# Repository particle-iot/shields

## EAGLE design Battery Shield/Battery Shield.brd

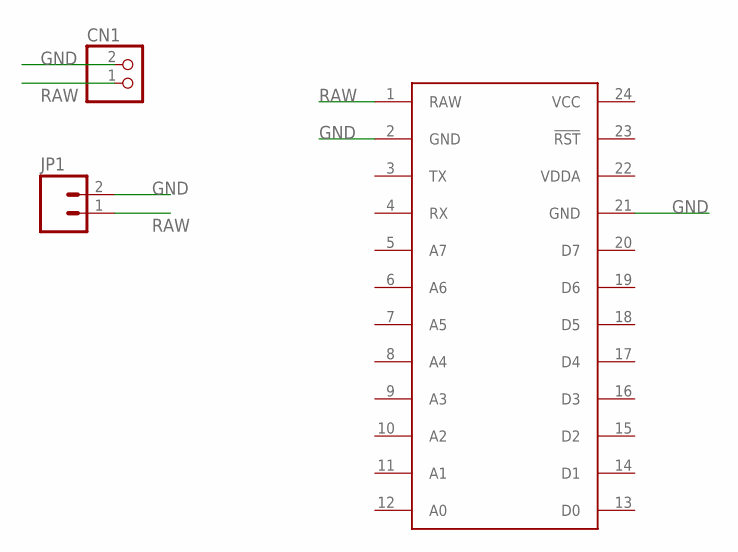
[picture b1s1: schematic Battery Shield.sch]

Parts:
CN1: JST_2PIN-THM; JST-PH-2-THM
JP1: M02PTH4; 1X02_XTRA_BIG
U$1: SPARK_CORECORE; SPARK_CORE

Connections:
GND: CN1.2 (1), JP1.2, U$1.2 (GND), U$1.21 (GND)
RAW: CN1.1 (2), JP1.1, U$1.1 (RAW)
VCC: U$1.24 (VCC)
VDDA: U$1.22 (VDDA)

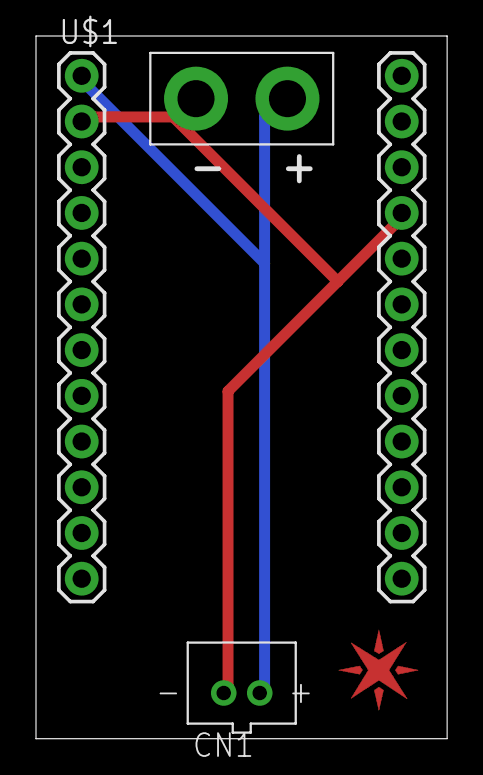
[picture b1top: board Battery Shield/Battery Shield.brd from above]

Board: 2 copper layers, 22.8 x 39.0 mm, 4 parts (0 on the bottom side), 2 nets.

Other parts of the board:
U$2: SPARK_LOGO_PLUS_PLANE

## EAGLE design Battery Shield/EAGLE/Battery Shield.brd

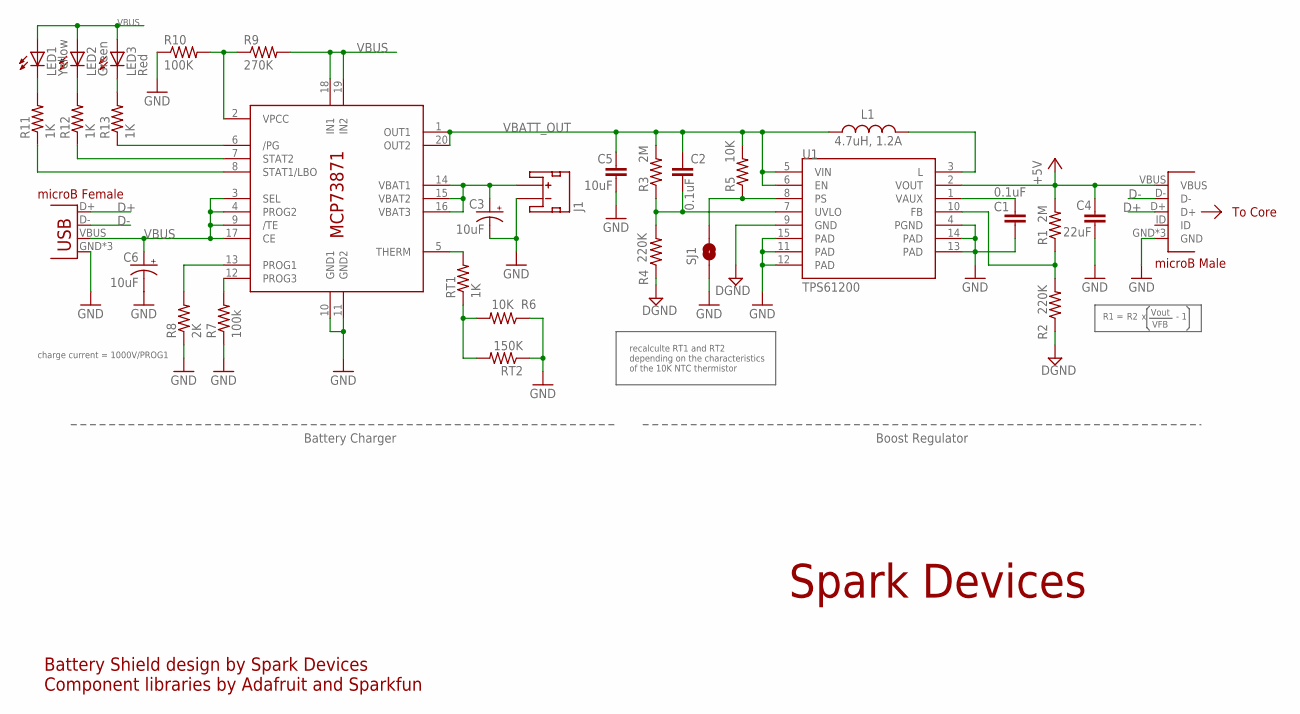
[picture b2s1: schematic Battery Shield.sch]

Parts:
C1, C2: 0.1uF; 0402-CAP
C3, C6: 10uF; EIA3216
C4: 22uF; 0805
C5: 10uF; 1206
IC1: MCP73871; QFN20
J1: JST_2MM_MALE; JST-2-SMD
JP1: USBUSB-MICROB-SLOT-HOLE; USB-MICROB-SLOT-HOLE
L1: 4.7uH, 1.2A; CDRH2D09
LED1: Yellow; LED-0603
LED2: Green; LED-0603
LED3: Red; LED-0603
R1, R3: 2M; 0402-RES
R2, R4: 220K; 0402-RES
R5, R6: 10K; 0402-RES
R7: 100k; 0402-RES
R8: 2K; 0402-RES
R9: 270K; 0402-RES
R10: 100K; 0402-RES
R11, R12, R13: 1K; 0402-RES
RT1: 1K; 0402-RES
RT2: 150K; 0402-RES
SJ1: SOLDERJUMPERNO; SJ_2S-NO
U1: TPS61200; QFN-10_PAD
U$1: USB_MALE; USB-MICROB-MALE-SANDWICH

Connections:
+5V: C4.1, R1.2, U1.2 (VOUT), U$1.VBUS; also elsewhere on the board
D+: JP1.D+, U$1.D+; also elsewhere on the board
D-: JP1.D-, U$1.D-; also elsewhere on the board
DGND: R2.1, R4.1, U1.9 (GND)
GND: C1.2, C3.C (-), C4.2, C5.2, C6.C (-), IC1.10 (GND1), IC1.11 (GND2), J1.1 (-), JP1.GND, JP1.MT1 (GND), JP1.MT2 (GND), R6.1, R7.1, R8.1, R10.1, RT2.1, SJ1.1, U1.4 (PGND), U1.11 (PAD), U1.12 (PAD), U1.13 (PAD), U1.14 (PAD), U1.15 (PAD), U$1.GND; also elsewhere on the board
unnamed: L1.P$2 (2), U1.3 (L)
unnamed: C1.1, U1.1 (VAUX)
unnamed: C2.2, R3.1, R4.2, U1.7 (UVLO)
unnamed: R1.1, R2.2, U1.10 (FB)
unnamed: C3.A (+), IC1.14 (VBAT1), IC1.15 (VBAT2), IC1.16 (VBAT3), J1.2 (+)
unnamed: IC1.8 (STAT1/LBO), R11.1
unnamed: R6.2, RT1.1, RT2.2
unnamed: LED1.C, R11.2
unnamed: IC1.5 (THERM), RT1.2
unnamed: LED2.C, R12.2
unnamed: IC1.12 (PROG3), R7.2
unnamed: IC1.2 (VPCC), R9.1, R10.2
unnamed: IC1.13 (PROG1), R8.2
unnamed: IC1.7 (STAT2), R12.1
unnamed: IC1.6 (/PG), R13.1
unnamed: LED3.C, R13.2
unnamed: R5.1, SJ1.2, U1.8 (PS)
VBATT_OUT: C2.1, C5.1, IC1.1 (OUT1), IC1.20 (OUT2), L1.P$1 (1), R3.2, R5.2, U1.5 (VIN), U1.6 (EN)
VBUS: C6.A (+), IC1.3 (SEL), IC1.4 (PROG2), IC1.9 (/TE), IC1.17 (CE), IC1.18 (IN1), IC1.19 (IN2), JP1.VBUS, LED1.A, LED2.A, LED3.A, R9.2

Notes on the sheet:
microB Male
microB Female
To Core
Battery Charger
Boost Regulator
recalculte RT1 and RT2 depending on the characteristics of the 10K NTC thermistor
charge current = 1000V/PROG1
R1 =
Vout
VFB
- 1
Spark Devices
Battery Shield design by Spark Devices Component libraries by Adafruit and Sparkfun

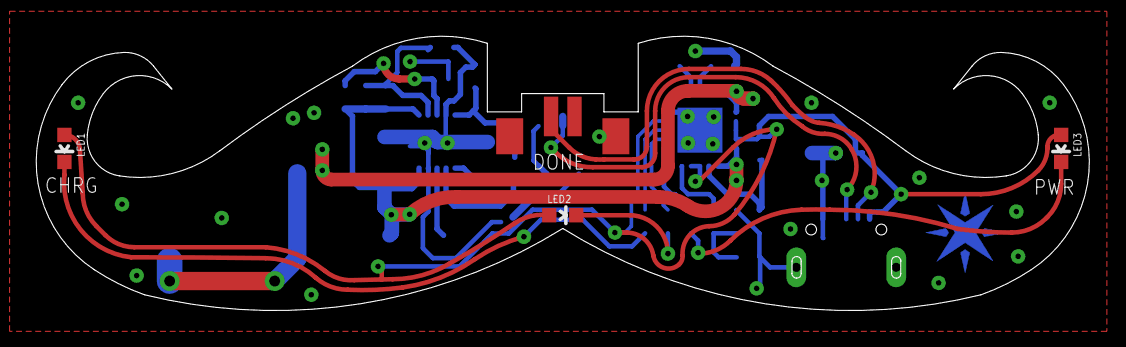
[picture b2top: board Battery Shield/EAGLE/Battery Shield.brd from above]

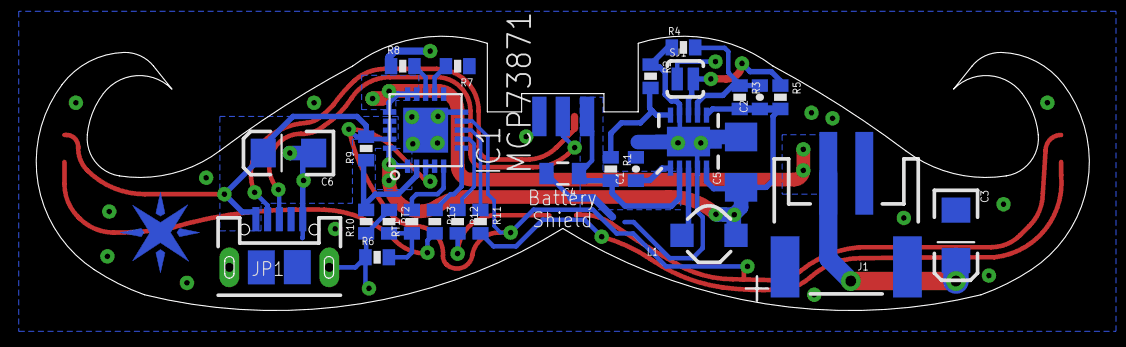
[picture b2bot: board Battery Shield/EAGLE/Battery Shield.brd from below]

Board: 2 copper layers, 58.5 x 15.2 mm, 32 parts (28 on the bottom side), 24 nets.

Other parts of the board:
JP2: USBFCI; USB-MICROB-MALE-SANDWICH
U$2: SPARK_LOGO_PLUS_PLANE

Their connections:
+5V: JP2.VBUS; also elsewhere on the board
D+: JP2.D+; also elsewhere on the board
D-: JP2.D-; also elsewhere on the board
GND: JP2.GND, JP2.GNDPAD1, JP2.GNDPAD2; also elsewhere on the board

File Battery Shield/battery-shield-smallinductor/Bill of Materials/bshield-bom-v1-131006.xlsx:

| PROJECT NAME |  | SPARK BATTERY SHIELD
 | LAST UPDATED |  | 41554
 | BSHIELD
 | Qty | AQS P/N | Device | Minimum Specification | Component Value (if different) | Package/Case | Designator | AVL | AVL P/N | Additional Comments
 | 1 | 307-20-301621 | Fab PCB | Double Sided, 1.0mm, 1OZ, Electroless Nickel Immersion Gold, Black Solder Mask,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 |  |  |  |  |  | CONSIGNED BY SPARK
 | 1 | HL-121-12-301353 | Ceramic Capacitor | 10uF, 10V, 10% |  | 1206 | C5 | Taiyo | LMK316BJ106KLHT
 | 2 | HL-121-02-301600 | Ceramic Capacitor | 0.1uF, 10V, 10% |  | 0402 | C1, C2 | RongFu | 0402B104K01A
 | 1 | HL-121-10-301613 | Ceramic Capacitor | 22uF, 10V, 10% |  | 0805 | C4 | Taiyo Yuden | LMK212BJ226MG-T
 | 1 | HL-221-90-301464 | DC to DC Booster | 1.2A |  | QFN10 Exposed Pad | U1 | Texas Instruments | TPS61200DRCT
 | 1 | 161-50-301205 | Inductor | 4.7uH, 25%, 1.0A |  | 3030 (3x3mm) | L1 | Sumida America | CDRH2D18/HPNP-4R7NC | CONSIGNED BY SPARK
 | 1 | HL-511-30-301381 | JST Right-Angle Connector | 2mm, 2-pin, Male, SMT |  | 2-Pin SMT, Right-Angle | J1 | Kaweei | CW2001-02T1-H01-B
 | 1 | HL-414-10-301291 | LED | Yellow |  | 0603 | LED1 | AQS supplier | WLUY0603A-25
 | 1 | HL-414-10-301292 | LED | Green |  | 0603 | LED2 | AQS supplier | WLG0603A-02-I
 | 1 | HL-414-10-301282 | LED | Blue |  | 0603 | LED3 | AQS supplier | WLUB0603A-341
 | 1 | HL-411-60-301004 | Li-Ion Rechargeable Battery | 3.7V, 400mAh, JST-PH-2P connector |  | JST-PH connector, 2-pin | BT1 | Pkcell | LP062530
 | 1 | 223-40-301231 | LiPo Charger | 4.4V-6.0V Input |  | QFN20 Exposed Pad (4x4) | IC1 | Microchip Technology | MCP73871T-2CCI/ML | CONSIGNED BY SPARK
 | 2 | HL-101-10-302444 | Resistor | 2M, 1%, 1/10W |  | 0402 | R1, R3 | Velox Vendor | SMD0402205F
 | 2 | HL-101-10-302445 | Resistor | 100K, 1%, 1/10W |  | 0402 | R7, R10 | Velox Vendor | SMD0402104F
 | 4 | HL-101-10-302446 | Resistor | 1K, 1%, 1/10W |  | 0402 | R11, R12, R13, RT1 | Velox Vendor | SMD0402102F
 | 2 | HL-101-10-302447 | Resistor | 220K, 1%, 1/10W |  | 0402 | R2, R4 | Velox Vendor | SMD0402223F
 | 1 | HL-101-10-302448 | Resistor | 2K, 1%, 1/10W |  | 0402 | R8 | Velox Vendor | SMD0402202F
 | 1 | HL-101-10-302449 | Resistor | 270K, 1%, 1/10W |  | 0402 | R9 | Velox Vendor | SMD0402273F
 | 1 | HL-101-10-302443 | Resistor | 150K, 1%, 1/10W |  | 0402 | RT2 | RongFu | 0402WAF0150KTCE
 | 1 | HL-101-10-302450 | Resistor | 10K, 1%, 1/10W |  | 0402 | R5, R6 | Panasonic Electronic Components | ERJ-2RKF1002X
 | 2 | HL-121-12-301350 | Tantalum Capacitor | 10uF, 16V, 10% |  | 1206 (3216) | C3, C6 | AVX | TAJA106K010RNJ.
 | 1 | HL-515-40-301729 | USB-Micro B Connector - Female | USB-Micro B, SMT with TH Board Guides |  | USB-MICROB | JP1 | Kaweei | CMCUSB-5BFM2G-01-D
 | 1 | 511-30-301385 | USB-Micro B Connector - Male | USB-Micro B, SMT with Sandwich Guides |  | USB-MICROB | JP2 | FCI | 10104109-0001LF | CONSIGNED BY SPARK
 | PACKAGING
 | Qty |  | Device | Minimum Specification | Component Value (if different) | Package/Case | Designator | AVL | AVL P/N | Additional Comments
 | 1 | HL-901-00-301327 | Small Static Bag |  |  | 130 x 100mm
 | 1 | HL-901-00-301332 | Small Static Bubble Bag |  |  | 110 x 140mm, red
 | 1 | 831-10-301388 | "STICK-BS" sticker | Shield Description and UPC Barcode |  | 8 x 10 cm |  |  |  | CONSIGNED BY SPARK

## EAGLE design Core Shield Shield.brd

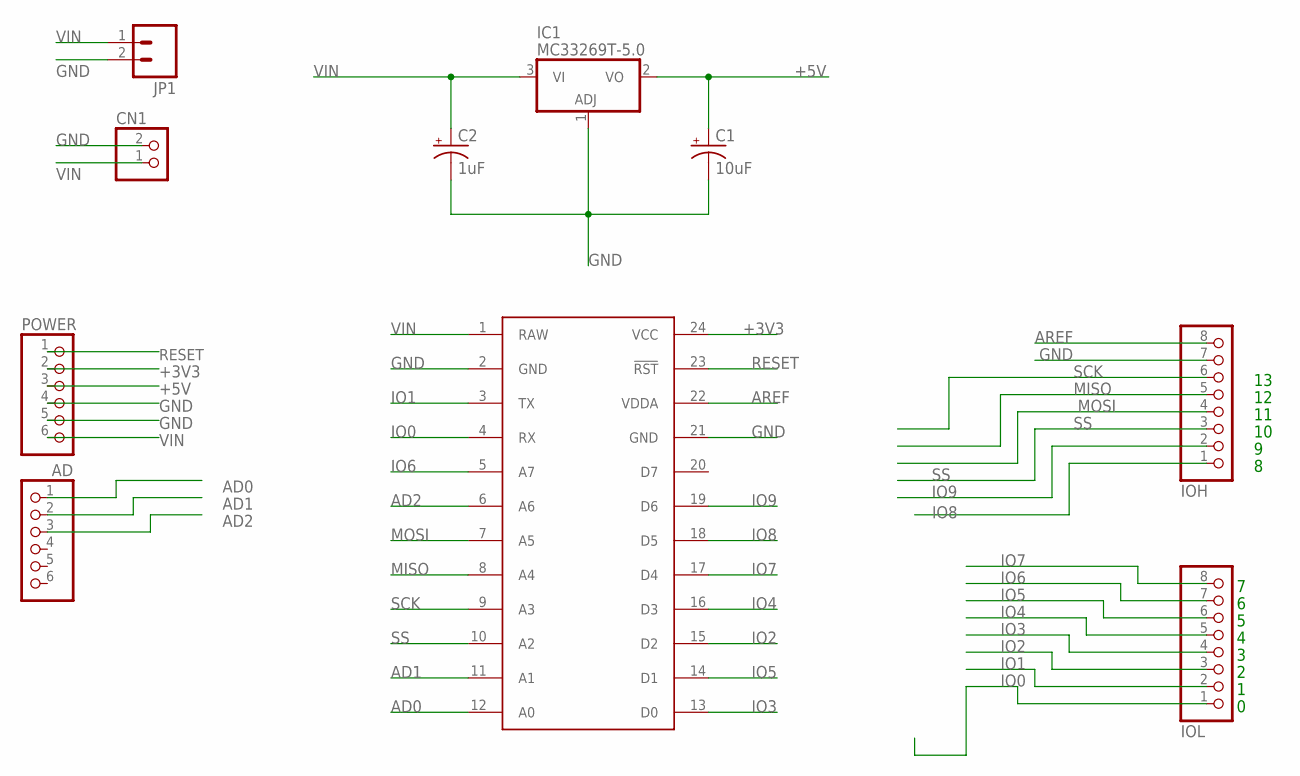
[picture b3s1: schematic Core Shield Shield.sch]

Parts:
AD: PINHD-1X6; 1X06
C1: 10uF; CPOL-RADIAL-10UF-25V
C2: 1uF; CPOL-RADIAL-10UF-25V
CN1: JST_2PIN-THM; JST-PH-2-THM
IC1: MC33269T-5.0; TO220V
IOH: PINHD-1X8; 1X08
IOL: PINHD-1X8; 1X08
JP1: M02LOCK; 1X02_LOCK
POWER: PINHD-1X6; 1X06
U$1: SPARK_CORECORE; SPARK_CORE

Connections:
+3V3: POWER.2, U$1.24 (VCC)
+5V: C1.1 (+), IC1.2 (VO), POWER.3
AD0: AD.1, U$1.12 (A0)
AD1: AD.2, U$1.11 (A1)
AD2: AD.3, U$1.6 (A6)
AREF: IOH.8, U$1.22 (VDDA)
GND: C1.2 (-), C2.2 (-), CN1.2 (1), IC1.1 (ADJ), IOH.7, JP1.2, POWER.4, POWER.5, U$1.2 (GND), U$1.21 (GND)
IO0: IOL.1, U$1.4 (RX)
IO1: IOL.2, U$1.3 (TX)
IO2: IOL.3, U$1.15 (D2)
IO3: IOL.4, U$1.13 (D0)
IO4: IOL.5, U$1.16 (D3)
IO5: IOL.6, U$1.14 (D1)
IO6: IOL.7, U$1.5 (A7)
IO7: IOL.8, U$1.17 (D4)
IO8: IOH.1, U$1.18 (D5)
IO9: IOH.2, U$1.19 (D6)
MISO: IOH.5, U$1.8 (A4)
MOSI: IOH.4, U$1.7 (A5)
RESET: POWER.1, U$1.23 (!RST)
SCK: IOH.6, U$1.9 (A3)
SS: IOH.3, U$1.10 (A2)
VIN: C2.1 (+), CN1.1 (2), IC1.3 (VI), JP1.1, POWER.6, U$1.1 (RAW)

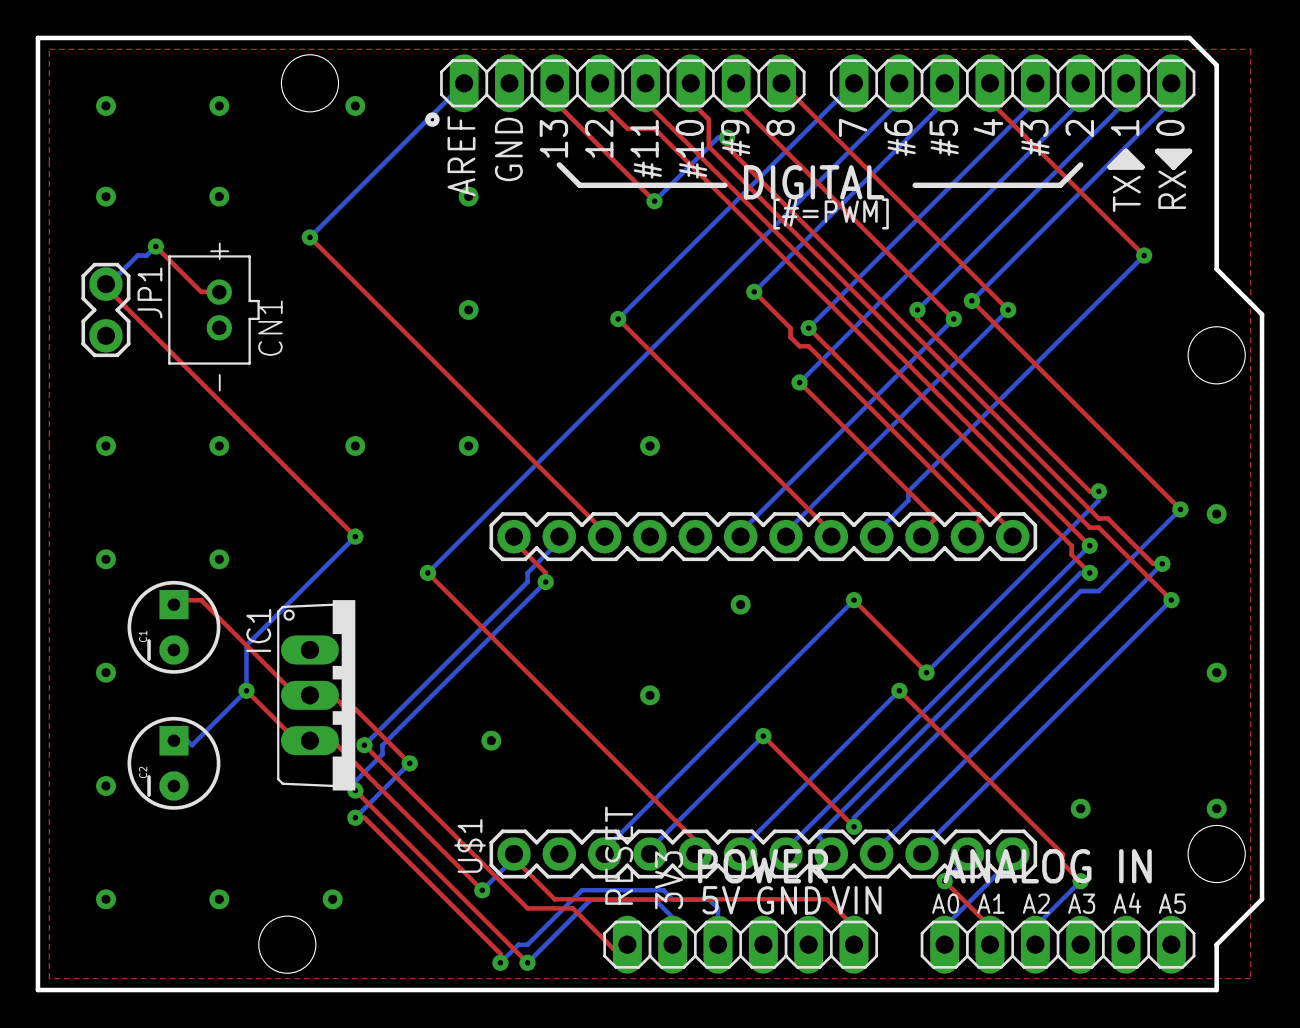
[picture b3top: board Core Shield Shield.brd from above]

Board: 2 copper layers, 68.6 x 53.3 mm, 10 parts (0 on the bottom side), 23 nets.

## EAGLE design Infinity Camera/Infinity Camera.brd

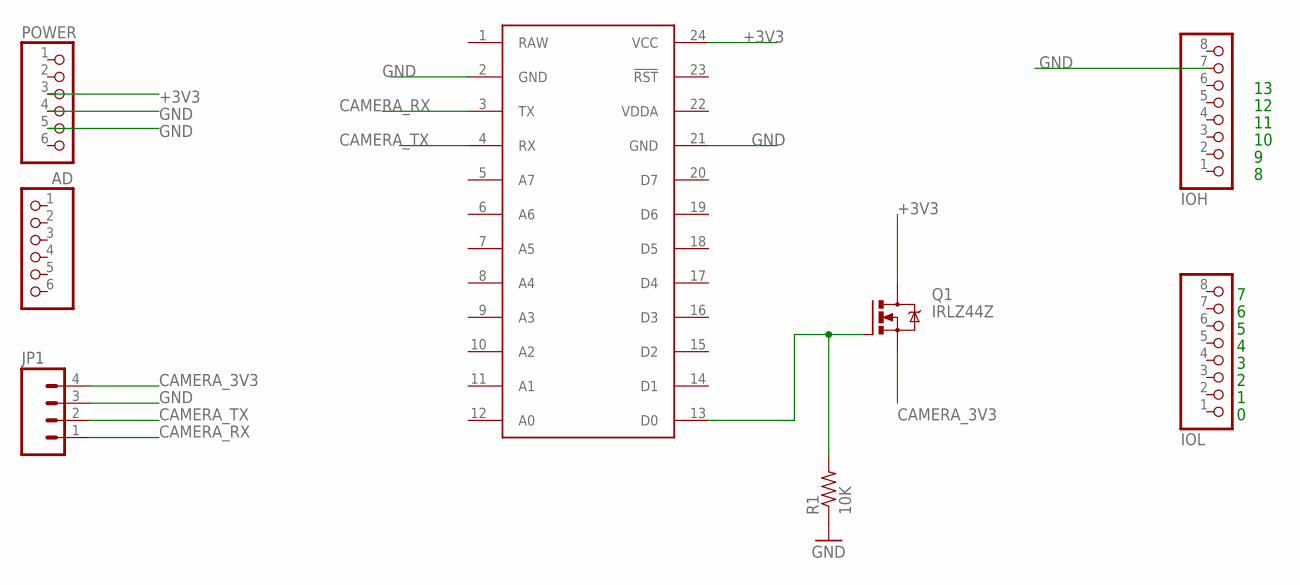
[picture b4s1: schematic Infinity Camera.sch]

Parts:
AD: PINHD-1X6; 1X06
IOH: PINHD-1X8; 1X08
IOL: PINHD-1X8; 1X08
JP1: M041.27MM; 1X04-1.27MM
POWER: PINHD-1X6; 1X06
Q1: IRLZ44Z; TO220BH
R1: 10K; AXIAL-0.4
U$1: SPARK_CORECORE; SPARK_CORE

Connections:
+3V3: POWER.3, Q1.D, U$1.24 (VCC)
CAMERA_3V3: JP1.4, Q1.S
CAMERA_RX: JP1.1, U$1.3 (TX)
CAMERA_TX: JP1.2, U$1.4 (RX)
GND: IOH.7, JP1.3, POWER.4, POWER.5, R1.P$1 (1), U$1.2 (GND), U$1.21 (GND)
unnamed: Q1.G, R1.P$2 (2), U$1.13 (D0)
RAW: U$1.1 (RAW)
VDDA: U$1.22 (VDDA)

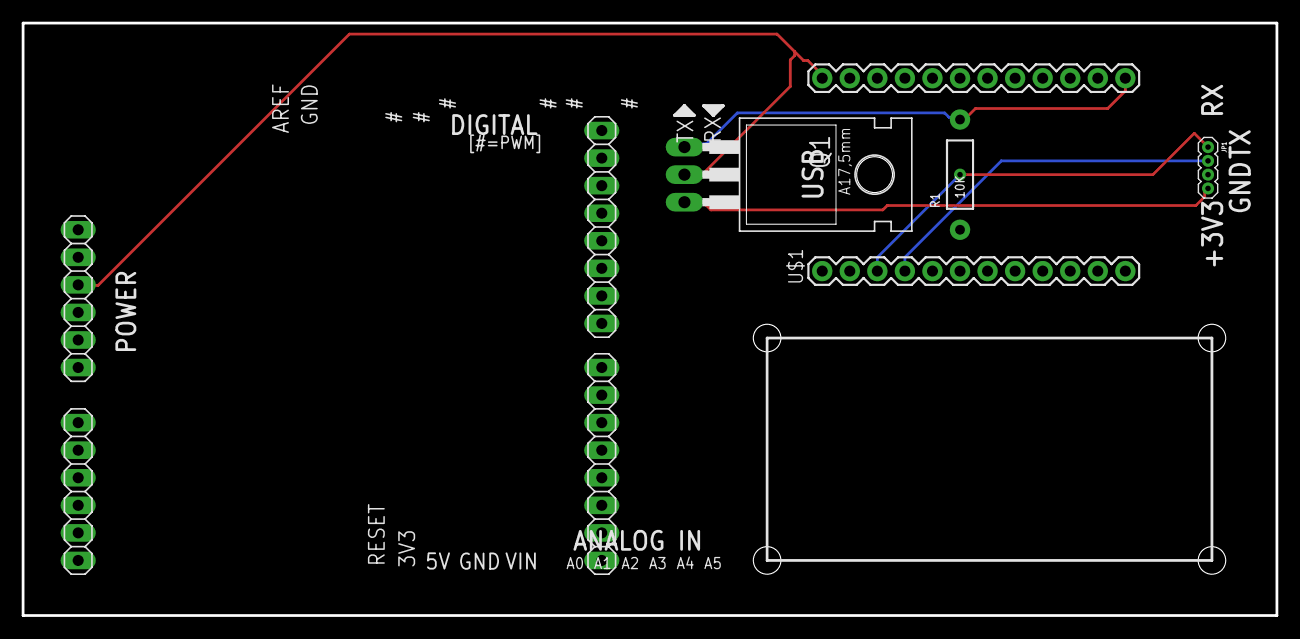
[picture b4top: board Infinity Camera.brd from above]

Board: 2 copper layers, 115.6 x 54.6 mm, 10 parts (0 on the bottom side), 6 nets.

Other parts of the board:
U$2, U$3: SPARK_LOGO

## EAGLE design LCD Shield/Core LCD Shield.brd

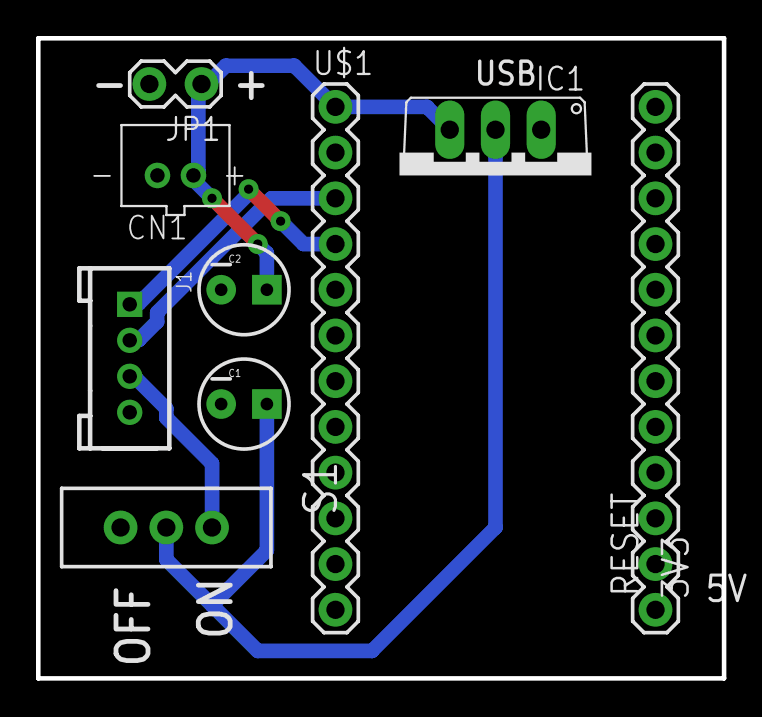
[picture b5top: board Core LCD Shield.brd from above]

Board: 2 copper layers, 38.1 x 35.6 mm, 9 parts (0 on the bottom side), 6 nets.

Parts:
C1: 10uF; CPOL-RADIAL-10UF-25V
C2: 1uF; CPOL-RADIAL-10UF-25V
CN1: JST-PH-2-THM
IC1: MC33269T-5.0; TO220V
J1: TWIG_2.0-DIP-FEMALE; 2.0_1X4
JP1: 1X02_LOCK
S1: SWITCH-SPDT
U$1: SPARK_CORECORE; SPARK_CORE
U$2: SPARK_LOGO

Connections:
+5V: J1.3, S1.1
GND: C1.2, C2.2, CN1.2, IC1.1, J1.4, JP1.2, U$1.2, U$1.21
N1: C1.1, IC1.2, S1.2
RX: J1.1, U$1.4
TX: J1.2, U$1.3
VIN: C2.1, CN1.1, IC1.3, JP1.1, U$1.1

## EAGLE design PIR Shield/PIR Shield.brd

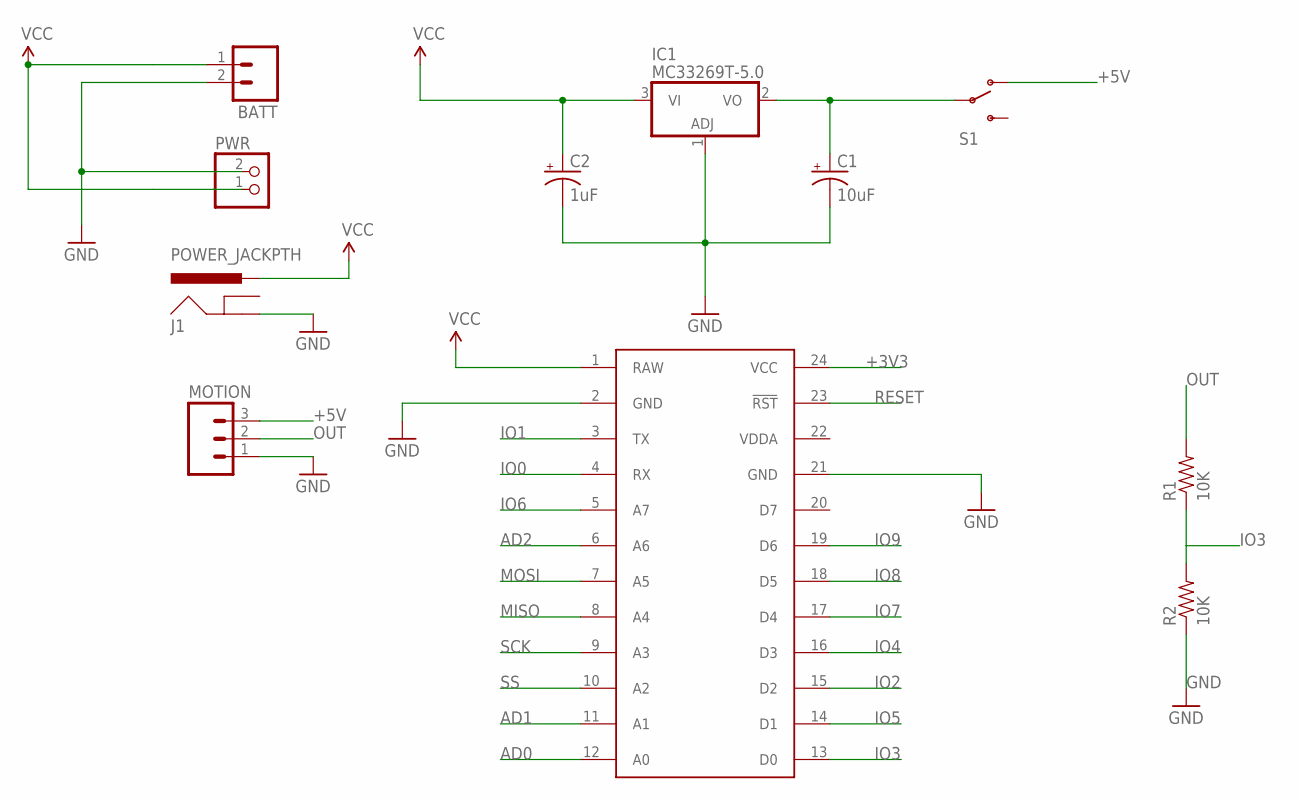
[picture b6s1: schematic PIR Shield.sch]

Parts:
BATT: M02LOCK; 1X02_LOCK
C1: 10uF; CPOL-RADIAL-10UF-25V
C2: 1uF; CPOL-RADIAL-10UF-25V
IC1: MC33269T-5.0; TO220V
J1: POWER_JACKPTH; POWER_JACK_PTH
MOTION: M03PTH; 1X03
PWR: JST_2PIN-THM; JST-PH-2-THM
R1, R2: 10K; AXIAL-0.3EZ
S1: SWITCH-SPDTPTH; SWITCH-SPDT
U$1: SPARK_CORECORE; SPARK_CORE

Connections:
+3V3: U$1.24 (VCC)
+5V: MOTION.3, S1.1 (O)
AD0: U$1.12 (A0)
AD1: U$1.11 (A1)
AD2: U$1.6 (A6)
GND: BATT.2, C1.2 (-), C2.2 (-), IC1.1 (ADJ), J1.GND, MOTION.1, PWR.2 (1), R2.P$1 (1), U$1.2 (GND), U$1.21 (GND)
IO0: U$1.4 (RX)
IO1: U$1.3 (TX)
IO2: U$1.15 (D2)
IO3: R1.P$1 (1), R2.P$2 (2), U$1.13 (D0)
IO4: U$1.16 (D3)
IO5: U$1.14 (D1)
IO6: U$1.5 (A7)
IO7: U$1.17 (D4)
IO8: U$1.18 (D5)
IO9: U$1.19 (D6)
MISO: U$1.8 (A4)
MOSI: U$1.7 (A5)
N1: C1.1 (+), IC1.2 (VO), S1.2
OUT: MOTION.2, R1.P$2 (2)
RESET: U$1.23 (!RST)
SCK: U$1.9 (A3)
SS: U$1.10 (A2)
VCC: BATT.1, C2.1 (+), IC1.3 (VI), J1.PWR, PWR.1 (2), U$1.1 (RAW)
VDDA: U$1.22 (VDDA)

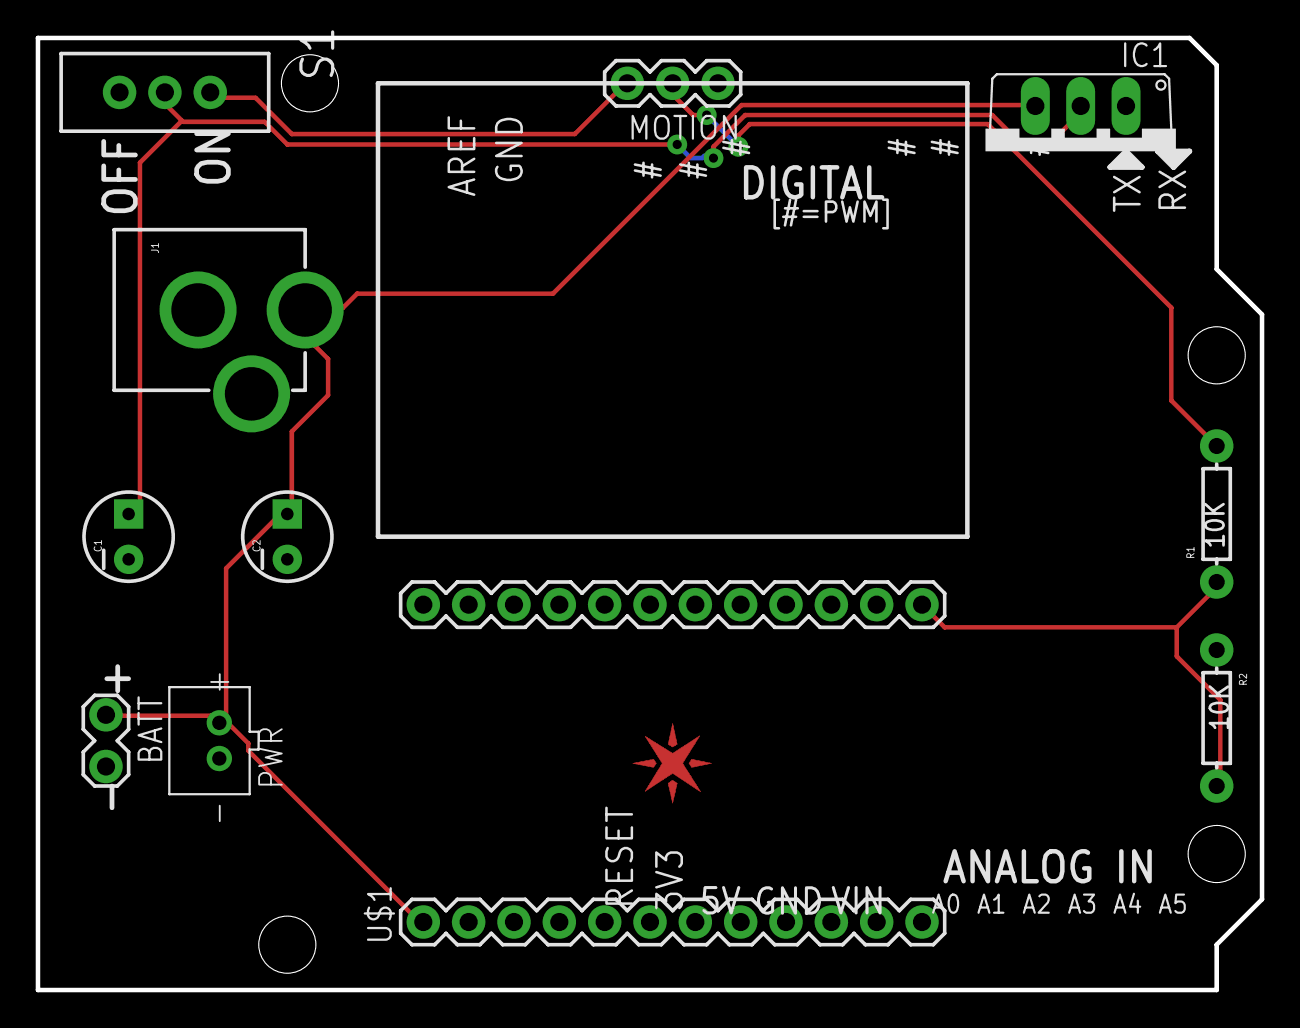
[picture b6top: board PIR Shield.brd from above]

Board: 2 copper layers, 68.6 x 53.3 mm, 13 parts (0 on the bottom side), 6 nets.

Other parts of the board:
U$2: SPARK_LOGO
U$3: SPARK_LOGO_PLUS_PLANE

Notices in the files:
parts and their libraries:
SparkFun-Connectors: Licensing: CC v3.0 Share-Alike You are welcome to use this library for commercial purposes.
